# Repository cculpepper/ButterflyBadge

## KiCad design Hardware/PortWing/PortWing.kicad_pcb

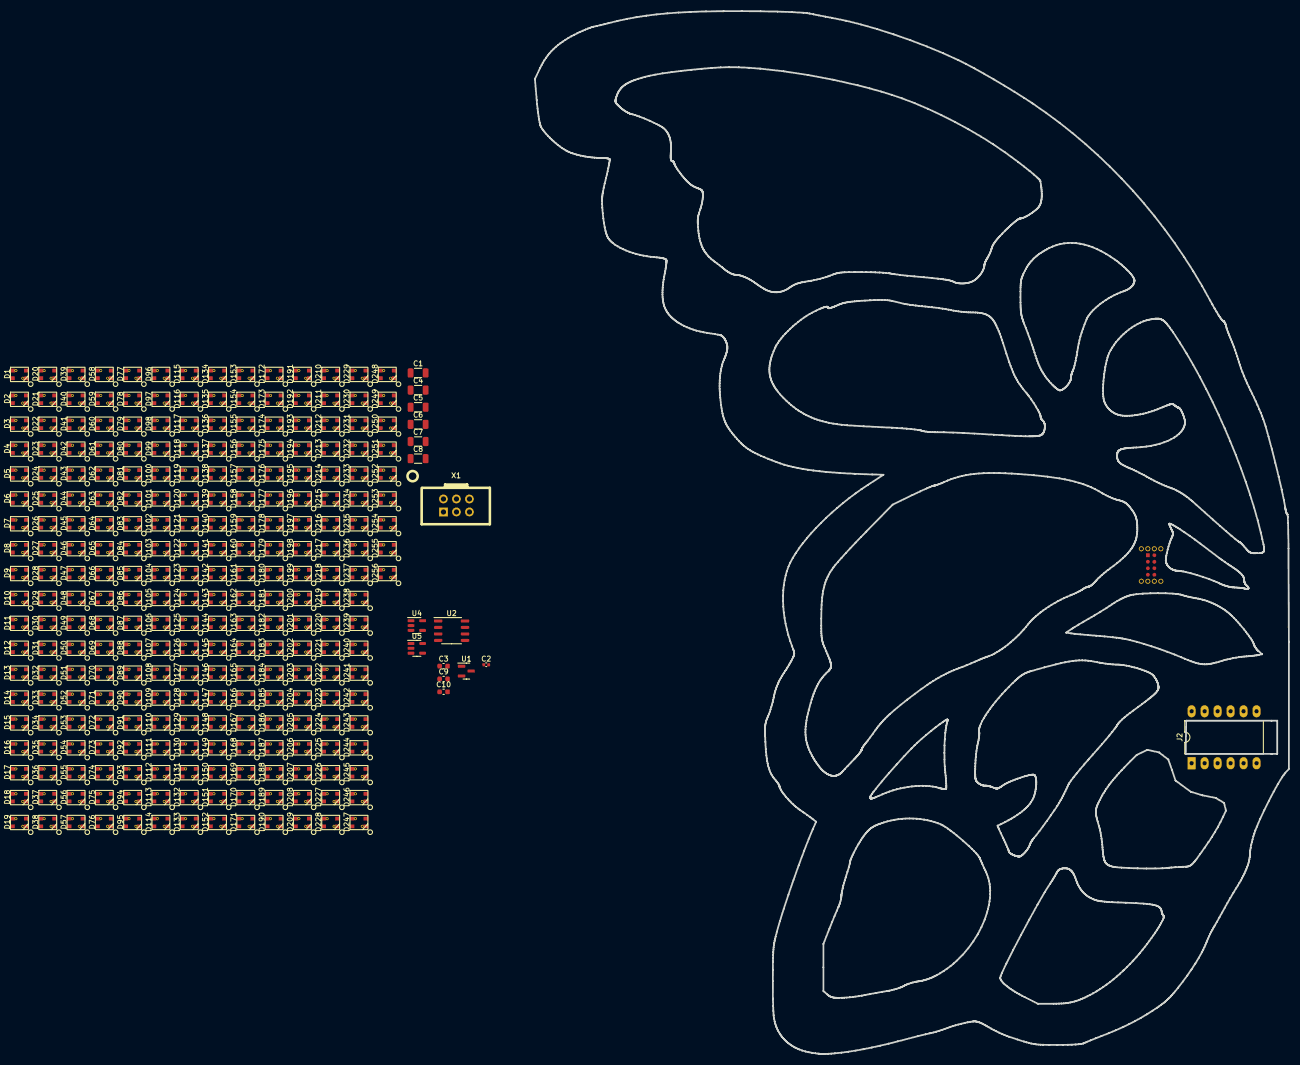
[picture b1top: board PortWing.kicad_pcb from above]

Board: 2 copper layers, 147.4 x 203.9 mm, 273 parts (0 on the bottom side), 265 nets, no tracks yet.

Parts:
C1, C4, C5, C6, C7, C8: 22uF; C_1206_3216Metric
C2: 1uF; C_0402_1005Metric
C3, C9, C10: 10uF; C_0603_1608Metric
D1, D2, D3, D4, D5, D6, D7, D8, D9, D10, D11, D12, D13, D14, D15, D16, D17, D18, D19, D20, D21, D22, D23, D24, D25, D26, D27, D28, D29, D30, D31, D32, D33, D34, D35, D36, D37, D38, D39, D40, D41, D42, D43, D44, D45, D46, D47, D48, D49, D50, D51, D52, D53, D54, D55, D56, D57, D58, D59, D60, D61, D62, D63, D64, D65, D66, D67, D68, D69, D70, D71, D72, D73, D74, D75, D76, D77, D78, D79, D80, D81, D82, D83, D84, D85, D86, D87, D88, D89, D90, D91, D92, D93, D94, D95, D96, D97, D98, D99, D100, D101, D102, D103, D104, D105, D106, D107, D108, D109, D110, D111, D112, D113, D114, D115, D116, D117, D118, D119, D120, D121, D122, D123, D124, D125, D126, D127, D128, D129, D130, D131, D132, D133, D134, D135, D136, D137, D138, D139, D140, D141, D142, D143, D144, D145, D146, D147, D148, D149, D150, D151, D152, D153, D154, D155, D156, D157, D158, D159, D160, D161, D162, D163, D164, D165, D166, D167, D168, D169, D170, D171, D172, D173, D174, D175, D176, D177, D178, D179, D180, D181, D182, D183, D184, D185, D186, D187, D188, D189, D190, D191, D192, D193, D194, D195, D196, D197, D198, D199, D200, D201, D202, D203, D204, D205, D206, D207, D208, D209, D210, D211, D212, D213, D214, D215, D216, D217, D218, D219, D220, D221, D222, D223, D224, D225, D226, D227, D228, D229, D230, D231, D232, D233, D234, D235, D236, D237, D238, D239, D240, D241, D242, D243, D244, D245, D246, D247, D248, D249, D250, D251, D252, D253, D254, D255, D256: SK6812; XL-3528RGBW
J1: Conn_02x04_Odd_Even; FlatFlexWingConnector-WingPCBSide
J2: Conn_02x06_Counter_Clockwise; DIP-12_W10.16mm_LongPads
U1: XC6206PxxxMR; SOT-23
U2: SOP-8_3.9x4.9mm_P1.27mm
U4, U5: SN74LV1T34DBV; SOT-23-5
X1: Badgelife_sao_connector_v169bis; Badgelife-SAOv169-BADGE-2x3

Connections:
/3V3: C2.1, C3.1, C9.1, C10.1, U1.2 (VO), U2.1 (V_EH), U2.8 (VCC), X1.1 (VCC)
/5V: C1.1, C4.1, C5.1, C6.1, C7.1, C8.1, D1.3 (VDD), D2.3 (VDD), D3.3 (VDD), D4.3 (VDD), D5.3 (VDD), D6.3 (VDD), D7.3 (VDD), D8.3 (VDD), D9.3 (VDD), D10.3 (VDD), D11.3 (VDD), D12.3 (VDD), D13.3 (VDD), D14.3 (VDD), D15.3 (VDD), D16.3 (VDD), D17.3 (VDD), D18.3 (VDD), D19.3 (VDD), D20.3 (VDD), D21.3 (VDD), D22.3 (VDD), D23.3 (VDD), D24.3 (VDD), D25.3 (VDD), D26.3 (VDD), D27.3 (VDD), D28.3 (VDD), D29.3 (VDD), D30.3 (VDD), D31.3 (VDD), D32.3 (VDD), D33.3 (VDD), D34.3 (VDD), D35.3 (VDD), D36.3 (VDD), D37.3 (VDD), D38.3 (VDD), D39.3 (VDD), D40.3 (VDD), D41.3 (VDD), D42.3 (VDD), D43.3 (VDD), D44.3 (VDD), D45.3 (VDD), D46.3 (VDD), D47.3 (VDD), D48.3 (VDD), D49.3 (VDD), D50.3 (VDD), D51.3 (VDD), D52.3 (VDD), D53.3 (VDD), D54.3 (VDD), D55.3 (VDD), D56.3 (VDD), D57.3 (VDD), D58.3 (VDD), D59.3 (VDD), D60.3 (VDD), D61.3 (VDD), D62.3 (VDD), D63.3 (VDD), D64.3 (VDD), D65.3 (VDD), D66.3 (VDD), D67.3 (VDD), D68.3 (VDD), D69.3 (VDD), D70.3 (VDD), D71.3 (VDD), D72.3 (VDD), D73.3 (VDD), D74.3 (VDD), D75.3 (VDD), D76.3 (VDD), D77.3 (VDD), D78.3 (VDD), D79.3 (VDD), D80.3 (VDD), D81.3 (VDD), D82.3 (VDD), D83.3 (VDD), D84.3 (VDD), D85.3 (VDD), D86.3 (VDD), D87.3 (VDD), D88.3 (VDD), D89.3 (VDD), D90.3 (VDD), D91.3 (VDD), D92.3 (VDD), D93.3 (VDD), D94.3 (VDD), D95.3 (VDD), D96.3 (VDD), D97.3 (VDD), D98.3 (VDD), D99.3 (VDD), D100.3 (VDD), D101.3 (VDD), D102.3 (VDD), D103.3 (VDD), D104.3 (VDD), D105.3 (VDD), D106.3 (VDD), D107.3 (VDD), D108.3 (VDD), D109.3 (VDD), D110.3 (VDD), D111.3 (VDD), D112.3 (VDD), D113.3 (VDD), D114.3 (VDD), D115.3 (VDD), D116.3 (VDD), D117.3 (VDD), D118.3 (VDD), D119.3 (VDD), D120.3 (VDD), D121.3 (VDD), D122.3 (VDD), D123.3 (VDD), D124.3 (VDD), D125.3 (VDD), D126.3 (VDD), D127.3 (VDD), D128.3 (VDD), D129.3 (VDD), D130.3 (VDD), D131.3 (VDD), D132.3 (VDD), D133.3 (VDD), D134.3 (VDD), D135.3 (VDD), D136.3 (VDD), D137.3 (VDD), D138.3 (VDD), D139.3 (VDD), D140.3 (VDD), D141.3 (VDD), D142.3 (VDD), D143.3 (VDD), D144.3 (VDD), D145.3 (VDD), D146.3 (VDD), D147.3 (VDD), D148.3 (VDD), D149.3 (VDD), D150.3 (VDD), D151.3 (VDD), D152.3 (VDD), D153.3 (VDD), D154.3 (VDD), D155.3 (VDD), D156.3 (VDD), D157.3 (VDD), D158.3 (VDD), D159.3 (VDD), D160.3 (VDD), D161.3 (VDD), D162.3 (VDD), D163.3 (VDD), D164.3 (VDD), D165.3 (VDD), D166.3 (VDD), D167.3 (VDD), D168.3 (VDD), D169.3 (VDD), D170.3 (VDD), D171.3 (VDD), D172.3 (VDD), D173.3 (VDD), D174.3 (VDD), D175.3 (VDD), D176.3 (VDD), D177.3 (VDD), D178.3 (VDD), D179.3 (VDD), D180.3 (VDD), D181.3 (VDD), D182.3 (VDD), D183.3 (VDD), D184.3 (VDD), D185.3 (VDD), D186.3 (VDD), D187.3 (VDD), D188.3 (VDD), D189.3 (VDD), D190.3 (VDD), D191.3 (VDD), D192.3 (VDD), D193.3 (VDD), D194.3 (VDD), D195.3 (VDD), D196.3 (VDD), D197.3 (VDD), D198.3 (VDD), D199.3 (VDD), D200.3 (VDD), D201.3 (VDD), D202.3 (VDD), D203.3 (VDD), D204.3 (VDD), D205.3 (VDD), D206.3 (VDD), D207.3 (VDD), D208.3 (VDD), D209.3 (VDD), D210.3 (VDD), D211.3 (VDD), D212.3 (VDD), D213.3 (VDD), D214.3 (VDD), D215.3 (VDD), D216.3 (VDD), D217.3 (VDD), D218.3 (VDD), D219.3 (VDD), D220.3 (VDD), D221.3 (VDD), D222.3 (VDD), D223.3 (VDD), D224.3 (VDD), D225.3 (VDD), D226.3 (VDD), D227.3 (VDD), D228.3 (VDD), D229.3 (VDD), D230.3 (VDD), D231.3 (VDD), D232.3 (VDD), D233.3 (VDD), D234.3 (VDD), D235.3 (VDD), D236.3 (VDD), D237.3 (VDD), D238.3 (VDD), D239.3 (VDD), D240.3 (VDD), D241.3 (VDD), D242.3 (VDD), D243.3 (VDD), D244.3 (VDD), D245.3 (VDD), D246.3 (VDD), D247.3 (VDD), D248.3 (VDD), D249.3 (VDD), D250.3 (VDD), D251.3 (VDD), D252.3 (VDD), D253.3 (VDD), D254.3 (VDD), D255.3 (VDD), D256.3 (VDD), J1.1, U1.3 (VI), U4.5 (VCC), U5.5 (VCC)
/GND: C1.2, C2.2, C3.2, C4.2, C5.2, C6.2, C7.2, C8.2, C9.2, C10.2, D1.1 (VSS), D2.1 (VSS), D3.1 (VSS), D4.1 (VSS), D5.1 (VSS), D6.1 (VSS), D7.1 (VSS), D8.1 (VSS), D9.1 (VSS), D10.1 (VSS), D11.1 (VSS), D12.1 (VSS), D13.1 (VSS), D14.1 (VSS), D15.1 (VSS), D16.1 (VSS), D17.1 (VSS), D18.1 (VSS), D19.1 (VSS), D20.1 (VSS), D21.1 (VSS), D22.1 (VSS), D23.1 (VSS), D24.1 (VSS), D25.1 (VSS), D26.1 (VSS), D27.1 (VSS), D28.1 (VSS), D29.1 (VSS), D30.1 (VSS), D31.1 (VSS), D32.1 (VSS), D33.1 (VSS), D34.1 (VSS), D35.1 (VSS), D36.1 (VSS), D37.1 (VSS), D38.1 (VSS), D39.1 (VSS), D40.1 (VSS), D41.1 (VSS), D42.1 (VSS), D43.1 (VSS), D44.1 (VSS), D45.1 (VSS), D46.1 (VSS), D47.1 (VSS), D48.1 (VSS), D49.1 (VSS), D50.1 (VSS), D51.1 (VSS), D52.1 (VSS), D53.1 (VSS), D54.1 (VSS), D55.1 (VSS), D56.1 (VSS), D57.1 (VSS), D58.1 (VSS), D59.1 (VSS), D60.1 (VSS), D61.1 (VSS), D62.1 (VSS), D63.1 (VSS), D64.1 (VSS), D65.1 (VSS), D66.1 (VSS), D67.1 (VSS), D68.1 (VSS), D69.1 (VSS), D70.1 (VSS), D71.1 (VSS), D72.1 (VSS), D73.1 (VSS), D74.1 (VSS), D75.1 (VSS), D76.1 (VSS), D77.1 (VSS), D78.1 (VSS), D79.1 (VSS), D80.1 (VSS), D81.1 (VSS), D82.1 (VSS), D83.1 (VSS), D84.1 (VSS), D85.1 (VSS), D86.1 (VSS), D87.1 (VSS), D88.1 (VSS), D89.1 (VSS), D90.1 (VSS), D91.1 (VSS), D92.1 (VSS), D93.1 (VSS), D94.1 (VSS), D95.1 (VSS), D96.1 (VSS), D97.1 (VSS), D98.1 (VSS), D99.1 (VSS), D100.1 (VSS), D101.1 (VSS), D102.1 (VSS), D103.1 (VSS), D104.1 (VSS), D105.1 (VSS), D106.1 (VSS), D107.1 (VSS), D108.1 (VSS), D109.1 (VSS), D110.1 (VSS), D111.1 (VSS), D112.1 (VSS), D113.1 (VSS), D114.1 (VSS), D115.1 (VSS), D116.1 (VSS), D117.1 (VSS), D118.1 (VSS), D119.1 (VSS), D120.1 (VSS), D121.1 (VSS), D122.1 (VSS), D123.1 (VSS), D124.1 (VSS), D125.1 (VSS), D126.1 (VSS), D127.1 (VSS), D128.1 (VSS), D129.1 (VSS), D130.1 (VSS), D131.1 (VSS), D132.1 (VSS), D133.1 (VSS), D134.1 (VSS), D135.1 (VSS), D136.1 (VSS), D137.1 (VSS), D138.1 (VSS), D139.1 (VSS), D140.1 (VSS), D141.1 (VSS), D142.1 (VSS), D143.1 (VSS), D144.1 (VSS), D145.1 (VSS), D146.1 (VSS), D147.1 (VSS), D148.1 (VSS), D149.1 (VSS), D150.1 (VSS), D151.1 (VSS), D152.1 (VSS), D153.1 (VSS), D154.1 (VSS), D155.1 (VSS), D156.1 (VSS), D157.1 (VSS), D158.1 (VSS), D159.1 (VSS), D160.1 (VSS), D161.1 (VSS), D162.1 (VSS), D163.1 (VSS), D164.1 (VSS), D165.1 (VSS), D166.1 (VSS), D167.1 (VSS), D168.1 (VSS), D169.1 (VSS), D170.1 (VSS), D171.1 (VSS), D172.1 (VSS), D173.1 (VSS), D174.1 (VSS), D175.1 (VSS), D176.1 (VSS), D177.1 (VSS), D178.1 (VSS), D179.1 (VSS), D180.1 (VSS), D181.1 (VSS), D182.1 (VSS), D183.1 (VSS), D184.1 (VSS), D185.1 (VSS), D186.1 (VSS), D187.1 (VSS), D188.1 (VSS), D189.1 (VSS), D190.1 (VSS), D191.1 (VSS), D192.1 (VSS), D193.1 (VSS), D194.1 (VSS), D195.1 (VSS), D196.1 (VSS), D197.1 (VSS), D198.1 (VSS), D199.1 (VSS), D200.1 (VSS), D201.1 (VSS), D202.1 (VSS), D203.1 (VSS), D204.1 (VSS), D205.1 (VSS), D206.1 (VSS), D207.1 (VSS), D208.1 (VSS), D209.1 (VSS), D210.1 (VSS), D211.1 (VSS), D212.1 (VSS), D213.1 (VSS), D214.1 (VSS), D215.1 (VSS), D216.1 (VSS), D217.1 (VSS), D218.1 (VSS), D219.1 (VSS), D220.1 (VSS), D221.1 (VSS), D222.1 (VSS), D223.1 (VSS), D224.1 (VSS), D225.1 (VSS), D226.1 (VSS), D227.1 (VSS), D228.1 (VSS), D229.1 (VSS), D230.1 (VSS), D231.1 (VSS), D232.1 (VSS), D233.1 (VSS), D234.1 (VSS), D235.1 (VSS), D236.1 (VSS), D237.1 (VSS), D238.1 (VSS), D239.1 (VSS), D240.1 (VSS), D241.1 (VSS), D242.1 (VSS), D243.1 (VSS), D244.1 (VSS), D245.1 (VSS), D246.1 (VSS), D247.1 (VSS), D248.1 (VSS), D249.1 (VSS), D250.1 (VSS), D251.1 (VSS), D252.1 (VSS), D253.1 (VSS), D254.1 (VSS), D255.1 (VSS), D256.1 (VSS), J1.3, U1.1 (GND), U2.4 (VSS), U4.3 (GND), U5.3 (GND), X1.2 (GND)
/NFC_MSG: J1.8, U2.7 (GP0), X1.6 (GPIO2)
/PORT_GP0: J1.6, X1.5 (GPIO1)
/PORT_LED_1: J1.2, U4.2 (A)
/PORT_LED_2: J1.4, U5.2 (A)
/SCL: J1.5, U2.6 (SCL), X1.4 (SCL)
/SDA: J1.7, U2.5 (SDA), X1.3 (SDA)
unnamed: D1.2 (DIN), U4.4 (Y)
unnamed: D1.4 (DOUT), D2.2 (DIN)
unnamed: D2.4 (DOUT), D3.2 (DIN)
unnamed: D3.4 (DOUT), D4.2 (DIN)
unnamed: D4.4 (DOUT), D5.2 (DIN)
unnamed: D5.4 (DOUT), D6.2 (DIN)
unnamed: D6.4 (DOUT), D7.2 (DIN)
unnamed: D7.4 (DOUT), D8.2 (DIN)
unnamed: D8.4 (DOUT), D9.2 (DIN)
unnamed: D9.4 (DOUT), D10.2 (DIN)
unnamed: D10.4 (DOUT), D11.2 (DIN)
unnamed: D11.4 (DOUT), D12.2 (DIN)
unnamed: D12.4 (DOUT), D13.2 (DIN)
unnamed: D13.4 (DOUT), D14.2 (DIN)
unnamed: D14.4 (DOUT), D15.2 (DIN)
unnamed: D15.4 (DOUT), D16.2 (DIN)
unnamed: D16.4 (DOUT), D17.2 (DIN)
unnamed: D17.4 (DOUT), D18.2 (DIN)
unnamed: D18.4 (DOUT), D19.2 (DIN)
unnamed: D19.4 (DOUT), D20.2 (DIN)
unnamed: D20.4 (DOUT), D21.2 (DIN)
unnamed: D21.4 (DOUT), D22.2 (DIN)
unnamed: D22.4 (DOUT), D23.2 (DIN)
unnamed: D23.4 (DOUT), D24.2 (DIN)
unnamed: D24.4 (DOUT), D25.2 (DIN)
unnamed: D25.4 (DOUT), D26.2 (DIN)
unnamed: D26.4 (DOUT), D27.2 (DIN)
unnamed: D27.4 (DOUT), D28.2 (DIN)
unnamed: D28.4 (DOUT), D29.2 (DIN)
unnamed: D29.4 (DOUT), D30.2 (DIN)
unnamed: D30.4 (DOUT), D31.2 (DIN)
unnamed: D31.4 (DOUT), D32.2 (DIN)
unnamed: D32.4 (DOUT), D33.2 (DIN)
unnamed: D33.4 (DOUT), D34.2 (DIN)
unnamed: D34.4 (DOUT), D35.2 (DIN)
unnamed: D35.4 (DOUT), D36.2 (DIN)
unnamed: D36.4 (DOUT), D37.2 (DIN)
unnamed: D37.4 (DOUT), D38.2 (DIN)
unnamed: D38.4 (DOUT), D39.2 (DIN)
unnamed: D39.4 (DOUT), D40.2 (DIN)
unnamed: D40.4 (DOUT), D41.2 (DIN)
unnamed: D41.4 (DOUT), D42.2 (DIN)
unnamed: D42.4 (DOUT), D43.2 (DIN)
unnamed: D43.4 (DOUT), D44.2 (DIN)
unnamed: D44.4 (DOUT), D45.2 (DIN)
unnamed: D45.4 (DOUT), D46.2 (DIN)
unnamed: D46.4 (DOUT), D47.2 (DIN)
unnamed: D47.4 (DOUT), D48.2 (DIN)
unnamed: D48.4 (DOUT), D49.2 (DIN)
unnamed: D49.4 (DOUT), D50.2 (DIN)
unnamed: D50.4 (DOUT), D51.2 (DIN)
unnamed: D51.4 (DOUT), D52.2 (DIN)
unnamed: D52.4 (DOUT), D53.2 (DIN)
unnamed: D53.4 (DOUT), D54.2 (DIN)
unnamed: D54.4 (DOUT), D55.2 (DIN)
unnamed: D55.4 (DOUT), D56.2 (DIN)
unnamed: D56.4 (DOUT), D57.2 (DIN)
unnamed: D57.4 (DOUT), D58.2 (DIN)
unnamed: D58.4 (DOUT), D59.2 (DIN)
unnamed: D59.4 (DOUT), D60.2 (DIN)
unnamed: D60.4 (DOUT), D61.2 (DIN)
unnamed: D61.4 (DOUT), D62.2 (DIN)
unnamed: D62.4 (DOUT), D63.2 (DIN)
unnamed: D63.4 (DOUT), D64.2 (DIN)
unnamed: D64.4 (DOUT), D65.2 (DIN)
unnamed: D65.4 (DOUT), D66.2 (DIN)
unnamed: D66.4 (DOUT), D67.2 (DIN)
unnamed: D67.4 (DOUT), D68.2 (DIN)
unnamed: D68.4 (DOUT), D69.2 (DIN)
unnamed: D69.4 (DOUT), D70.2 (DIN)
unnamed: D70.4 (DOUT), D71.2 (DIN)
unnamed: D71.4 (DOUT), D72.2 (DIN)
unnamed: D72.4 (DOUT), D73.2 (DIN)
unnamed: D73.4 (DOUT), D74.2 (DIN)
unnamed: D74.4 (DOUT), D75.2 (DIN)
unnamed: D75.4 (DOUT), D76.2 (DIN)
unnamed: D76.4 (DOUT), D77.2 (DIN)
unnamed: D77.4 (DOUT), D78.2 (DIN)
unnamed: D78.4 (DOUT), D79.2 (DIN)
unnamed: D79.4 (DOUT), D80.2 (DIN)
unnamed: D80.4 (DOUT), D81.2 (DIN)
unnamed: D81.4 (DOUT), D82.2 (DIN)
unnamed: D82.4 (DOUT), D83.2 (DIN)
unnamed: D83.4 (DOUT), D84.2 (DIN)
unnamed: D84.4 (DOUT), D85.2 (DIN)
unnamed: D85.4 (DOUT), D86.2 (DIN)
unnamed: D86.4 (DOUT), D87.2 (DIN)
unnamed: D87.4 (DOUT), D88.2 (DIN)
unnamed: D88.4 (DOUT), D89.2 (DIN)
unnamed: D89.4 (DOUT), D90.2 (DIN)
unnamed: D90.4 (DOUT), D91.2 (DIN)
unnamed: D91.4 (DOUT), D92.2 (DIN)
unnamed: D92.4 (DOUT), D93.2 (DIN)
unnamed: D93.4 (DOUT), D94.2 (DIN)
unnamed: D94.4 (DOUT), D95.2 (DIN)
unnamed: D95.4 (DOUT), D96.2 (DIN)
unnamed: D96.4 (DOUT), D97.2 (DIN)
unnamed: D97.4 (DOUT), D98.2 (DIN)
unnamed: D98.4 (DOUT), D99.2 (DIN)
unnamed: D99.4 (DOUT), D100.2 (DIN)
unnamed: D100.4 (DOUT), D101.2 (DIN)
unnamed: D101.4 (DOUT), D102.2 (DIN)
unnamed: D102.4 (DOUT), D103.2 (DIN)
unnamed: D103.4 (DOUT), D104.2 (DIN)
unnamed: D104.4 (DOUT), D105.2 (DIN)
unnamed: D105.4 (DOUT), D106.2 (DIN)
unnamed: D106.4 (DOUT), D107.2 (DIN)
unnamed: D107.4 (DOUT), D108.2 (DIN)
unnamed: D108.4 (DOUT), D109.2 (DIN)
unnamed: D109.4 (DOUT), D110.2 (DIN)
unnamed: D110.4 (DOUT), D111.2 (DIN)
unnamed: D111.4 (DOUT), D112.2 (DIN)
unnamed: D112.4 (DOUT), D113.2 (DIN)
unnamed: D113.4 (DOUT), D114.2 (DIN)
unnamed: D114.4 (DOUT), D115.2 (DIN)
unnamed: D115.4 (DOUT), D116.2 (DIN)
unnamed: D116.4 (DOUT), D117.2 (DIN)
unnamed: D117.4 (DOUT), D118.2 (DIN)
unnamed: D118.4 (DOUT), D119.2 (DIN)
unnamed: D119.4 (DOUT), D120.2 (DIN)
unnamed: D120.4 (DOUT), D121.2 (DIN)
unnamed: D121.4 (DOUT), D122.2 (DIN)
unnamed: D122.4 (DOUT), D123.2 (DIN)
unnamed: D123.4 (DOUT), D124.2 (DIN)
unnamed: D124.4 (DOUT), D125.2 (DIN)
unnamed: D125.4 (DOUT), D126.2 (DIN)
unnamed: D126.4 (DOUT), D127.2 (DIN)
unnamed: D127.4 (DOUT), D128.2 (DIN)
unnamed: D129.2 (DIN), U5.4 (Y)
unnamed: D129.4 (DOUT), D130.2 (DIN)
unnamed: D130.4 (DOUT), D131.2 (DIN)
unnamed: D131.4 (DOUT), D132.2 (DIN)
unnamed: D132.4 (DOUT), D133.2 (DIN)
unnamed: D133.4 (DOUT), D134.2 (DIN)
unnamed: D134.4 (DOUT), D135.2 (DIN)
unnamed: D135.4 (DOUT), D136.2 (DIN)
unnamed: D136.4 (DOUT), D137.2 (DIN)
unnamed: D137.4 (DOUT), D138.2 (DIN)
unnamed: D138.4 (DOUT), D139.2 (DIN)
unnamed: D139.4 (DOUT), D140.2 (DIN)
unnamed: D140.4 (DOUT), D141.2 (DIN)
unnamed: D141.4 (DOUT), D142.2 (DIN)
unnamed: D142.4 (DOUT), D143.2 (DIN)
unnamed: D143.4 (DOUT), D144.2 (DIN)
unnamed: D144.4 (DOUT), D145.2 (DIN)
unnamed: D145.4 (DOUT), D146.2 (DIN)
unnamed: D146.4 (DOUT), D147.2 (DIN)
unnamed: D147.4 (DOUT), D148.2 (DIN)
unnamed: D148.4 (DOUT), D149.2 (DIN)
unnamed: D149.4 (DOUT), D150.2 (DIN)
unnamed: D150.4 (DOUT), D151.2 (DIN)
unnamed: D151.4 (DOUT), D152.2 (DIN)
unnamed: D152.4 (DOUT), D153.2 (DIN)
unnamed: D153.4 (DOUT), D154.2 (DIN)
unnamed: D154.4 (DOUT), D155.2 (DIN)
unnamed: D155.4 (DOUT), D156.2 (DIN)
unnamed: D156.4 (DOUT), D157.2 (DIN)
unnamed: D157.4 (DOUT), D158.2 (DIN)
unnamed: D158.4 (DOUT), D159.2 (DIN)
unnamed: D159.4 (DOUT), D160.2 (DIN)
unnamed: D160.4 (DOUT), D161.2 (DIN)
unnamed: D161.4 (DOUT), D162.2 (DIN)
unnamed: D162.4 (DOUT), D163.2 (DIN)
unnamed: D163.4 (DOUT), D164.2 (DIN)
unnamed: D164.4 (DOUT), D165.2 (DIN)
unnamed: D165.4 (DOUT), D166.2 (DIN)
unnamed: D166.4 (DOUT), D167.2 (DIN)
unnamed: D167.4 (DOUT), D168.2 (DIN)
unnamed: D168.4 (DOUT), D169.2 (DIN)
unnamed: D169.4 (DOUT), D170.2 (DIN)
unnamed: D170.4 (DOUT), D171.2 (DIN)
unnamed: D171.4 (DOUT), D172.2 (DIN)
unnamed: D172.4 (DOUT), D173.2 (DIN)
unnamed: D173.4 (DOUT), D174.2 (DIN)
unnamed: D174.4 (DOUT), D175.2 (DIN)
unnamed: D175.4 (DOUT), D176.2 (DIN)
unnamed: D176.4 (DOUT), D177.2 (DIN)
unnamed: D177.4 (DOUT), D178.2 (DIN)
unnamed: D178.4 (DOUT), D179.2 (DIN)
unnamed: D179.4 (DOUT), D180.2 (DIN)
unnamed: D180.4 (DOUT), D181.2 (DIN)
unnamed: D181.4 (DOUT), D182.2 (DIN)
unnamed: D182.4 (DOUT), D183.2 (DIN)
unnamed: D183.4 (DOUT), D184.2 (DIN)
unnamed: D184.4 (DOUT), D185.2 (DIN)
unnamed: D185.4 (DOUT), D186.2 (DIN)
unnamed: D186.4 (DOUT), D187.2 (DIN)
unnamed: D187.4 (DOUT), D188.2 (DIN)
unnamed: D188.4 (DOUT), D189.2 (DIN)
unnamed: D189.4 (DOUT), D190.2 (DIN)
unnamed: D190.4 (DOUT), D191.2 (DIN)
unnamed: D191.4 (DOUT), D192.2 (DIN)
unnamed: D192.4 (DOUT), D193.2 (DIN)
unnamed: D193.4 (DOUT), D194.2 (DIN)
unnamed: D194.4 (DOUT), D195.2 (DIN)
unnamed: D195.4 (DOUT), D196.2 (DIN)
unnamed: D196.4 (DOUT), D197.2 (DIN)
unnamed: D197.4 (DOUT), D198.2 (DIN)
unnamed: D198.4 (DOUT), D199.2 (DIN)
unnamed: D199.4 (DOUT), D200.2 (DIN)
unnamed: D200.4 (DOUT), D201.2 (DIN)
unnamed: D201.4 (DOUT), D202.2 (DIN)
unnamed: D202.4 (DOUT), D203.2 (DIN)
unnamed: D203.4 (DOUT), D204.2 (DIN)
unnamed: D204.4 (DOUT), D205.2 (DIN)
unnamed: D205.4 (DOUT), D206.2 (DIN)
unnamed: D206.4 (DOUT), D207.2 (DIN)
unnamed: D207.4 (DOUT), D208.2 (DIN)
unnamed: D208.4 (DOUT), D209.2 (DIN)
unnamed: D209.4 (DOUT), D210.2 (DIN)
unnamed: D210.4 (DOUT), D211.2 (DIN)
unnamed: D211.4 (DOUT), D212.2 (DIN)
unnamed: D212.4 (DOUT), D213.2 (DIN)
unnamed: D213.4 (DOUT), D214.2 (DIN)
unnamed: D214.4 (DOUT), D215.2 (DIN)
unnamed: D215.4 (DOUT), D216.2 (DIN)
unnamed: D216.4 (DOUT), D217.2 (DIN)
unnamed: D217.4 (DOUT), D218.2 (DIN)
unnamed: D218.4 (DOUT), D219.2 (DIN)
unnamed: D219.4 (DOUT), D220.2 (DIN)
unnamed: D220.4 (DOUT), D221.2 (DIN)
unnamed: D221.4 (DOUT), D222.2 (DIN)
unnamed: D222.4 (DOUT), D223.2 (DIN)
unnamed: D223.4 (DOUT), D224.2 (DIN)
unnamed: D224.4 (DOUT), D225.2 (DIN)
unnamed: D225.4 (DOUT), D226.2 (DIN)
unnamed: D226.4 (DOUT), D227.2 (DIN)
unnamed: D227.4 (DOUT), D228.2 (DIN)
unnamed: D228.4 (DOUT), D229.2 (DIN)
unnamed: D229.4 (DOUT), D230.2 (DIN)
unnamed: D230.4 (DOUT), D231.2 (DIN)
unnamed: D231.4 (DOUT), D232.2 (DIN)
unnamed: D232.4 (DOUT), D233.2 (DIN)
unnamed: D233.4 (DOUT), D234.2 (DIN)
unnamed: D234.4 (DOUT), D235.2 (DIN)
unnamed: D235.4 (DOUT), D236.2 (DIN)
unnamed: D236.4 (DOUT), D237.2 (DIN)
unnamed: D237.4 (DOUT), D238.2 (DIN)
unnamed: D238.4 (DOUT), D239.2 (DIN)
unnamed: D239.4 (DOUT), D240.2 (DIN)
unnamed: D240.4 (DOUT), D241.2 (DIN)
unnamed: D241.4 (DOUT), D242.2 (DIN)
unnamed: D242.4 (DOUT), D243.2 (DIN)
unnamed: D243.4 (DOUT), D244.2 (DIN)
unnamed: D244.4 (DOUT), D245.2 (DIN)
unnamed: D245.4 (DOUT), D246.2 (DIN)
unnamed: D246.4 (DOUT), D247.2 (DIN)
unnamed: D247.4 (DOUT), D248.2 (DIN)
unnamed: D248.4 (DOUT), D249.2 (DIN)
unnamed: D249.4 (DOUT), D250.2 (DIN)
unnamed: D250.4 (DOUT), D251.2 (DIN)
unnamed: D251.4 (DOUT), D252.2 (DIN)
unnamed: D252.4 (DOUT), D253.2 (DIN)
unnamed: D253.4 (DOUT), D254.2 (DIN)
unnamed: D254.4 (DOUT), D255.2 (DIN)
unnamed: D255.4 (DOUT), D256.2 (DIN)

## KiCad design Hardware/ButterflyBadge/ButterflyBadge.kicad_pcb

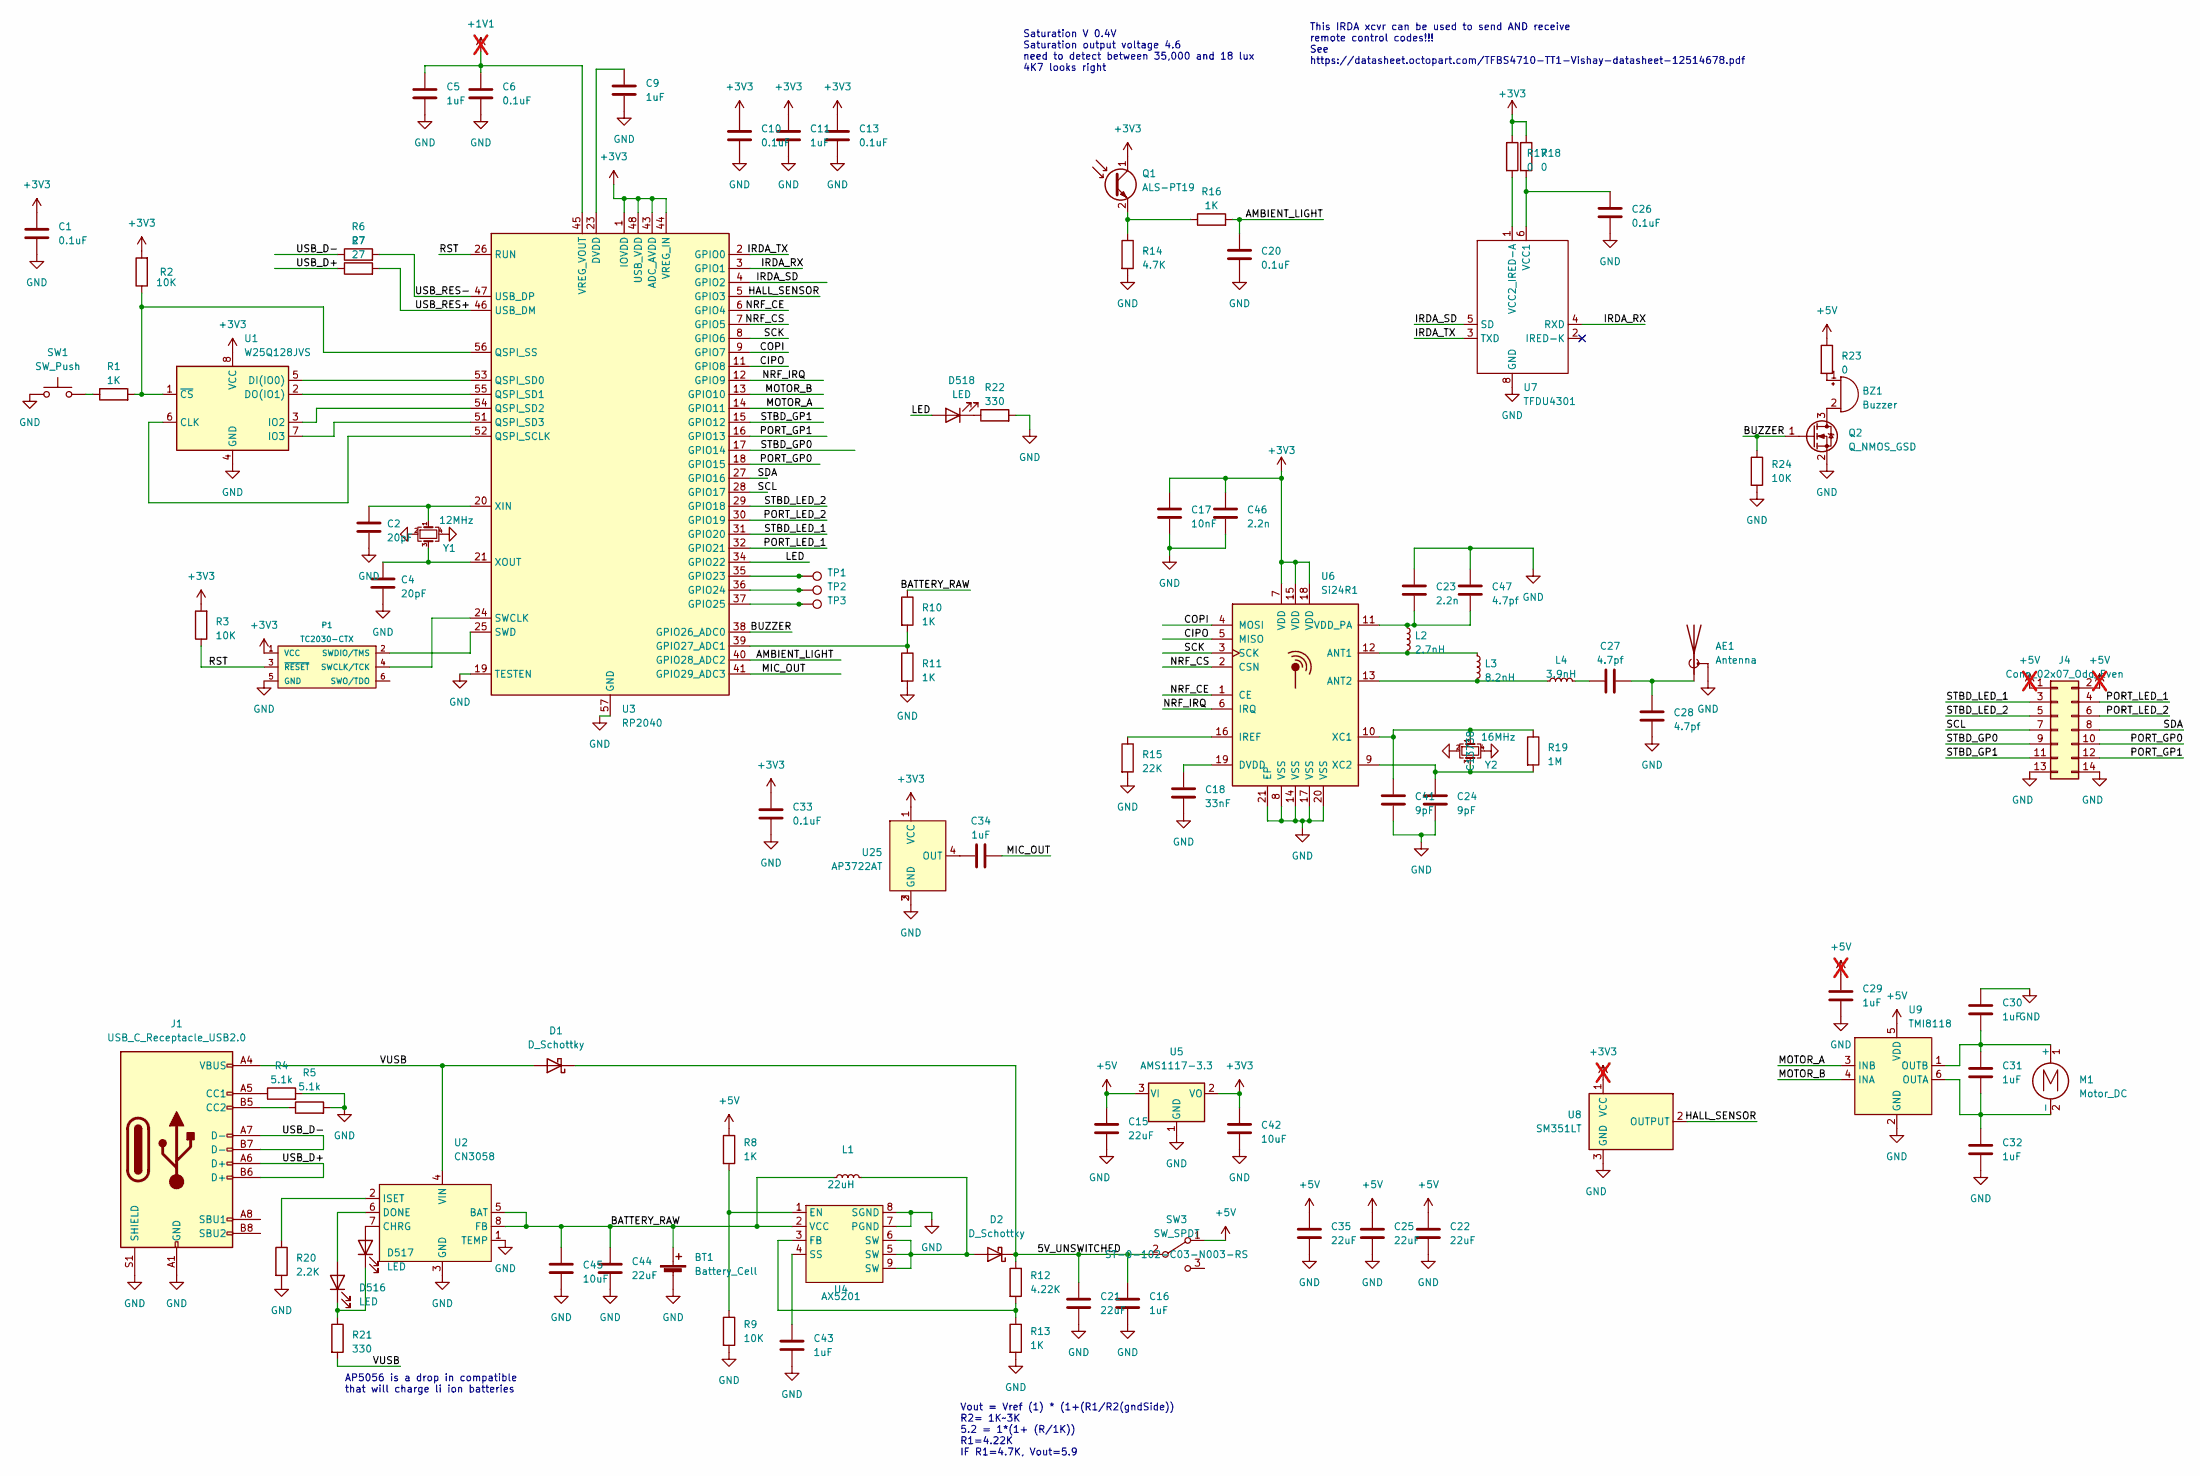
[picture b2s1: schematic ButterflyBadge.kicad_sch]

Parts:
AE1: Antenna; Texas_SWRA117D_2.4GHz_Left
BT1: Battery_Cell; BatteryHolder_MPD_BH-18650-PC2
BZ1: Buzzer; Buzzer-GSC5025YA-12R4000
C1, C6, C10, C13, C20, C33: 0.1uF; C_0402_1005Metric; LCSC C307331
C2, C4: 20pF; C_0402_1005Metric; LCSC C1554
C5, C9, C11, C16, C29, C30, C31, C32, C34, C43: 1uF; C_0402_1005Metric; LCSC C52923
C15, C21, C22, C25, C35, C44: 22uF; C_1206_3216Metric; LCSC C12891
C17: 10nF; C_0402_1005Metric; LCSC C15195
C18: 33nF; C_0402_1005Metric; LCSC C1585
C23, C46: 2.2n; C_0402_1005Metric; LCSC C1531
C24, C41: 9pF; C_0402_1005Metric; LCSC C32949
C26: 0.1uF; C_0603_1608Metric; LCSC C307331
C27, C28, C47: 4.7pf; C_0402_1005Metric; LCSC C1569
C42, C45: 10uF; C_0603_1608Metric; LCSC C96446
D1, D2: D_Schottky; D_SMA; LCSC C8678
D516, D517, D518: LED; LED_0603_1608Metric; LCSC C2286
J1: USB_C_Receptacle_USB2.0; USB_C_Receptacle_HRO_TYPE-C-31-M-12
J4: Conn_02x07_Odd_Even; FlatFlexWingConnector-PCBSide
L1: 22uH; YSPI0630A; LCSC C497873
L2: 2.7nH; L_0402_1005Metric; LCSC C14033
L3: 8.2nH; L_0402_1005Metric; LCSC C27147
L4: 3.9nH; L_0402_1005Metric; LCSC C14033
M1: Motor_DC; JST_XH_B2B-XH-AM_1x02_P2.50mm_Vertical
P1: TC2030-CTX; TC2030-MCP-NL
Q1: ALS-PT19; R_0402_1005Metric; Manufacturer PN ALS-PT19-315C/L177/TR8; LCSC C146233
Q2: Q_NMOS_GSD; SOT-23; LCSC C8545
R1, R8, R10, R11, R13, R16: 1K; R_0402_1005Metric; LCSC C11702
R2, R3, R9, R24: 10K; R_0402_1005Metric; LCSC C25744
R4, R5: 5.1k; R_0402_1005Metric; LCSC C25905
R6, R7: 27; R_0402_1005Metric; LCSC C25105
R12: 4.22K; R_0402_1005Metric; LCSC C25900
R14: 4.7K; R_0402_1005Metric; LCSC C25900
R15: 22K; R_0402_1005Metric; LCSC C25768
R17, R18, R23: 0; R_0402_1005Metric; LCSC C17168
R19: 1M; R_0402_1005Metric; LCSC C26083
R20: 2.2K; C_0402_1005Metric; LCSC C25879
R21, R22: 330; C_0402_1005Metric; LCSC C25104
SW1: SW_Push; SW_SPST_EVPBF; LCSC C318884
SW3: SW_SPDT; SW_Push_1P2T_Vertical_E-Switch_800UDP8P1A1M6; Manufacturer PN ST-0-102-C03-N003-RS
TP1, TP2, TP3: TestPoint_Pad_D1.0mm
U1: W25Q128JVS; SOIC-8_5.23x5.23mm_P1.27mm; LCSC C97521
U2: CN3058; SOP-8_3.9x4.9mm_P1.27mm; LCSC CN3058E
U3: RP2040; QFN-56-1EP_7x7mm_P0.4mm_EP3.2x3.2mm; LCSC C2040
U4: AX5201; SOIC-8-1EP_3.9x4.9mm_P1.27mm_EP2.41x3.3mm_ThermalVias; LCSC C211668
U5: AMS1117-3.3; SOT-223-3_TabPin2; LCSC C6186
U6: Si24R1; QFN-20-1EP_4x4mm_P0.5mm_EP2.5x2.5mm; LCSC C14436
U7: TFDU4301; LCSC C222418
U8: SM351LT; SOT-23; LCSC C285995
U9: TMI8118; SOT-23-6; LCSC C840556
U25: AP3722AT; LCSC C918198
Y1: 12MHz; Crystal_SMD_3225-4Pin_3.2x2.5mm; LCSC C9002
Y2: 16MHz; Crystal_SMD_3225-4Pin_3.2x2.5mm; LCSC C13738

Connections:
+1V1: C5.1, C6.1, U3.45 (VREG_VOUT)
+3V3: C1.1, C10.1, C11.1, C13.1, C17.1, C33.1, C42.1, C46.1, P1.1 (VCC), Q1.1 (C), R2.2, R3.2, R17.1, R18.1, U1.8 (VCC), U3.1 (IOVDD), U3.10 (IOVDD), U3.22 (IOVDD), U3.33 (IOVDD), U3.42 (IOVDD), U3.43 (ADC_AVDD), U3.44 (VREG_IN), U3.48 (USB_VDD), U3.49 (IOVDD), U5.2 (VO), U6.7 (VDD), U6.15 (VDD), U6.18 (VDD), U8.1 (VCC), U25.1 (VCC)
+5V: C15.1, C22.1, C25.1, C29.1, C35.1, J4.1, J4.2, R8.1, R23.1, SW3.1 (A), U5.3 (VI), U9.5 (VDD)
/5V_UNSWITCHED: C16.1, C21.1, D1.1 (K), D2.1 (K), R12.1, SW3.2 (B)
/AMBIENT_LIGHT: C20.1, R16.2, U3.40 (GPIO28_ADC2)
/BATTERY_RAW: BT1.1 (+), C44.1, C45.1, L1.1, R10.1, U2.5 (BAT), U2.8 (FB), U4.2 (VCC)
/BUZZER: Q2.1 (G), R24.1, U3.38 (GPIO26_ADC0)
/CIPO: U3.11 (GPIO8), U6.5 (MISO)
/COPI: U3.9 (GPIO7), U6.4 (MOSI)
/HALL_SENSOR: U3.5 (GPIO3), U8.2 (OUTPUT)
/IRDA_RX: U3.3 (GPIO1), U7.4 (RXD)
/IRDA_SD: U3.4 (GPIO2), U7.5 (SD)
/IRDA_TX: U3.2 (GPIO0), U7.3 (TXD)
/LED: D518.2 (A), U3.34 (GPIO22)
/MIC_OUT: C34.2, U3.41 (GPIO29_ADC3)
/MOTOR_A: U3.14 (GPIO11), U9.3 (INB)
/MOTOR_B: U3.13 (GPIO10), U9.4 (INA)
/NRF_CE: U3.6 (GPIO4), U6.1 (CE)
/NRF_CS: U3.7 (GPIO5), U6.2 (CSN)
/NRF_IRQ: U3.12 (GPIO9), U6.6 (IRQ)
/PORT_GP0: J4.10, U3.18 (GPIO15)
/PORT_GP1: J4.12, U3.16 (GPIO13)
/PORT_LED_1: J4.4, U3.32 (GPIO21)
/PORT_LED_2: J4.6, U3.30 (GPIO19)
/RST: P1.3 (~RESET), R3.1, U3.26 (RUN)
/SCK: U3.8 (GPIO6), U6.3 (SCK)
/SCL: J4.7, U3.28 (GPIO17)
/SDA: J4.8, U3.27 (GPIO16)
/STBD_GP0: J4.9, U3.17 (GPIO14)
/STBD_GP1: J4.11, U3.15 (GPIO12)
/STBD_LED_1: J4.3, U3.31 (GPIO20)
/STBD_LED_2: J4.5, U3.29 (GPIO18)
/USB_D+: J1.A6 (D+), J1.B6 (D+), R7.1
/USB_D-: J1.A7 (D-), J1.B7 (D-), R6.1
/USB_RES+: R7.2, U3.46 (USB_DM)
/USB_RES-: R6.2, U3.47 (USB_DP)
/VUSB: D1.2 (A), J1.A4 (VBUS), J1.A9 (VBUS), J1.B4 (VBUS), J1.B9 (VBUS), R21.2, U2.4 (VIN)
GND: AE1.2 (Shield), BT1.2 (-), C1.2, C2.2, C4.2, C5.2, C6.2, C9.2, C10.2, C11.2, C13.2, C15.2, C16.2, C17.2, C18.2, C20.2, C21.2, C22.2, C23.1, C24.2, C25.2, C26.2, C28.1, C29.2, C30.1, C32.2, C33.2, C35.2, C41.2, C42.2, C43.2, C44.2, C45.2, C46.2, C47.2, J1.A1 (GND), J1.A12 (GND), J1.B1 (GND), J1.B12 (GND), J1.S1 (SHIELD), J4.13, J4.14, P1.5 (GND), Q2.2 (S), R4.2, R5.2, R9.2, R11.2, R13.2, R14.2, R15.2, R20.2, R22.2, R24.2, SW1.1, U1.4 (GND), U2.1 (TEMP), U2.3 (GND), U3.19 (TESTEN), U3.57 (GND), U4.7 (PGND), U4.8 (SGND), U5.1 (GND), U6.8 (VSS), U6.14 (VSS), U6.17 (VSS), U6.20 (VSS), U6.21 (EP), U7.8 (GND), U8.3 (GND), U9.2 (GND), U25.2 (GND), U25.3 (GND), Y1.2, Y1.4, Y2.2, Y2.4
unnamed: AE1.1 (A), C27.2, C28.2
unnamed: BZ1.2 (+), Q2.3 (D)
unnamed: BZ1.1 (-), R23.2
unnamed: C27.1, L4.2
unnamed: D2.2 (A), L1.2, U4.5 (SW), U4.6 (SW), U4.9 (SW)
unnamed: D516.2 (A), U2.6 (DONE)
unnamed: D516.1 (K), D517.1 (K), R21.1
unnamed: D517.2 (A), U2.7 (CHRG)
unnamed: D518.1 (K), R22.1
unnamed: J1.A5 (CC1), R4.1
unnamed: J1.B5 (CC2), R5.1
unnamed: C30.2, C31.1, M1.1 (+), U9.1 (OUTB)
unnamed: C31.2, C32.1, M1.2 (-), U9.6 (OUTA)
unnamed: P1.4 (SWCLK/TCK), U3.24 (SWCLK)
unnamed: P1.2 (SWDIO/TMS), U3.25 (SWD)
unnamed: Q1.2 (E), R14.1, R16.1
unnamed: R1.1, SW1.2
unnamed: U1.6 (CLK), U3.52 (QSPI_SCLK)
unnamed: U1.5 (DI(IO0)), U3.53 (QSPI_SD0)
unnamed: U1.2 (DO(IO1)), U3.55 (QSPI_SD1)
unnamed: U1.3 (IO2), U3.54 (QSPI_SD2)
unnamed: U1.7 (IO3), U3.51 (QSPI_SD3)
unnamed: R1.2, R2.1, U1.1 (~CS), U3.56 (QSPI_SS)
unnamed: R20.1, U2.2 (ISET)
unnamed: C9.1, U3.23 (DVDD), U3.50 (DVDD)
unnamed: TP1.1, U3.35 (GPIO23)
unnamed: TP2.1, U3.36 (GPIO24)
unnamed: TP3.1, U3.37 (GPIO25)
unnamed: R10.2, R11.1, U3.39 (GPIO27_ADC1)
unnamed: C2.1, U3.20 (XIN), Y1.1
unnamed: C4.1, U3.21 (XOUT), Y1.3
unnamed: R8.2, R9.1, U4.1 (EN)
unnamed: R12.2, R13.1, U4.3 (FB)
unnamed: C43.1, U4.4 (SS)
unnamed: L2.2, L3.1, U6.12 (ANT1)
unnamed: L3.2, L4.1, U6.13 (ANT2)
unnamed: C18.1, U6.19 (DVDD)
unnamed: R15.1, U6.16 (IREF)
unnamed: C23.2, C47.1, L2.1, U6.11 (VDD_PA)
unnamed: C41.1, R19.1, U6.10 (XC1), Y2.1
unnamed: C24.1, R19.2, U6.9 (XC2), Y2.3
unnamed: C26.1, R18.2, U7.6 (VCC1)
unnamed: R17.2, U7.1 (VCC2_IRED-A)
unnamed: C34.1, U25.4 (OUT)

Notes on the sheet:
Vout = Vref (1) * (1+(R1/R2(gndSide)) R2= 1K~3K 5.2 = 1*(1+ (R/1K)) R1=4.22K IF R1=4.7K, Vout=5.9
AP5056 is a drop in compatible that will charge li ion batteries
This IRDA xcvr can be used to send AND receive remote control codes!!! See https://datasheet.octopart.com/TFBS4710-TT1-Vishay-datasheet-12514678.pdf
Saturation V 0.4V Saturation output voltage 4.6 need to detect between 35,000 and 18 lux 4K7 looks right

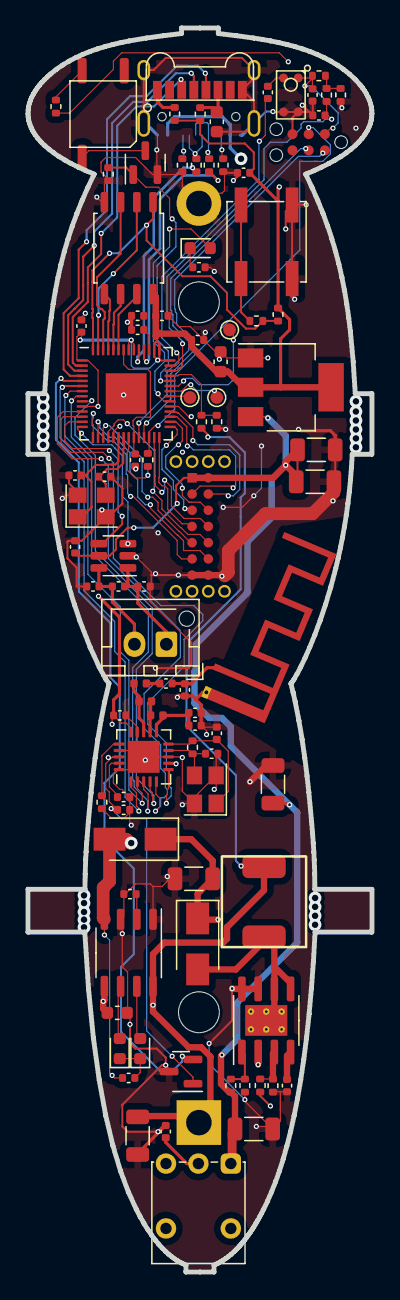
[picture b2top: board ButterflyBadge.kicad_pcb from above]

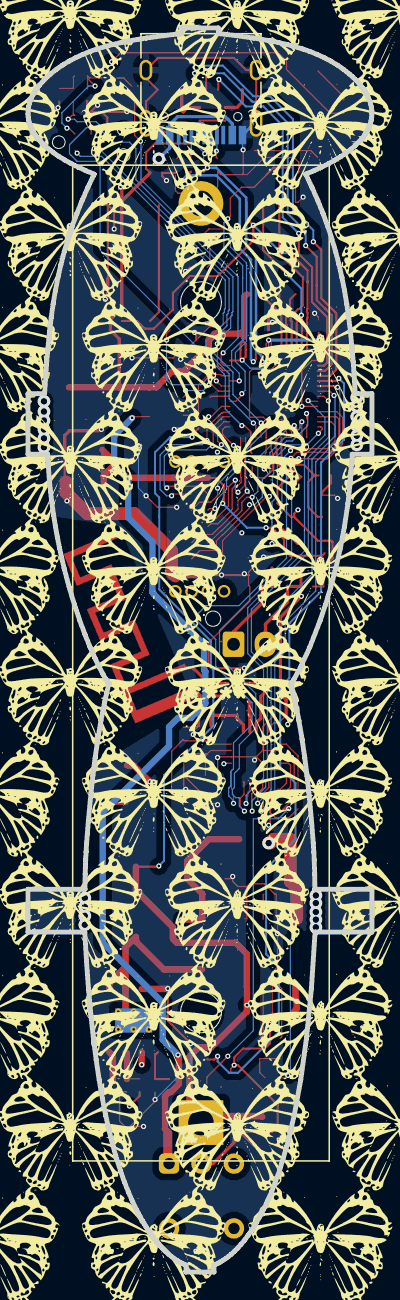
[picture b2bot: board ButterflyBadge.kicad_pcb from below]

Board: 4 copper layers, 26.9 x 97.4 mm, 95 parts (2 on the bottom side), 82 nets.

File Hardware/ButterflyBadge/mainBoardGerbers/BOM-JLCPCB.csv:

Comment,Designator,Footprint,LCSC
"Antenna","AE1","RF_Antenna:Texas_SWRA117D_2.4GHz_Left",""
"Battery_Cell","BT1","Battery:BatteryHolder_MPD_BH-18650-PC2",""
"Buzzer","BZ1","ButterflyBadge:Buzzer-GSC5025YA-12R4000",""
"0.1uF","C1,C6,C10,C13,C20,C33","Capacitor_SMD:C_0402_1005Metric","C307331"
"22uF","C15,C21,C22,C25,C35,C44","Capacitor_SMD:C_1206_3216Metric","C12891"
"10nF","C17","Capacitor_SMD:C_0402_1005Metric","C15195"
"33nF","C18","Capacitor_SMD:C_0402_1005Metric","C1585"
"20pF","C2,C4","Capacitor_SMD:C_0402_1005Metric","C1554"
"2.2n","C23,C46","Capacitor_SMD:C_0402_1005Metric","C1531"
"9pF","C24,C41","Capacitor_SMD:C_0402_1005Metric","C32949"
"0.1uF","C26","Capacitor_SMD:C_0603_1608Metric","C307331"
"4.7pf","C27,C28,C47","Capacitor_SMD:C_0402_1005Metric","C1569"
"10uF","C42,C45","Capacitor_SMD:C_0603_1608Metric","C96446"
"1uF","C5,C9,C11,C16,C29,C30,C31,C32,C34,C43","Capacitor_SMD:C_0402_1005Metric","C52923"
"D_Schottky","D1,D2","Diode_SMD:D_SMA","C8678"
"LED","D516,D517,D518","LED_SMD:LED_0603_1608Metric","C2286"
"USB_C_Receptacle_USB2.0","J1","Connector_USB:USB_C_Receptacle_HRO_TYPE-C-31-M-12",""
"Conn_02x07_Odd_Even","J4","ButterflyBadge:FlatFlexWingConnector-PCBSide",""
"22uH","L1","ButterflyBadge:YSPI0630A","C497873"
"2.7nH","L2","Inductor_SMD:L_0402_1005Metric","C14033"
"8.2nH","L3","Inductor_SMD:L_0402_1005Metric","C27147"
"3.9nH","L4","Inductor_SMD:L_0402_1005Metric","C14033"
"Motor_DC","M1","Connector_JST:JST_XH_B2B-XH-AM_1x02_P2.50mm_Vertical",""
"TC2030-CTX","P1","Tag-Connect:TC2030-MCP-NL",""
"ALS-PT19","Q1","Resistor_SMD:R_0402_1005Metric","C146233"
"Q_NMOS_GSD","Q2","Package_TO_SOT_SMD:SOT-23","C8545"
"1K","R1,R8,R10,R11,R13,R16","Resistor_SMD:R_0402_1005Metric","C11702"
"4.22K","R12","Resistor_SMD:R_0402_1005Metric","C25900"
"4.7K","R14","Resistor_SMD:R_0402_1005Metric","C25900"
"22K","R15","Resistor_SMD:R_0402_1005Metric","C25768"
"0","R17,R18,R23","Resistor_SMD:R_0402_1005Metric","C17168"
"1M","R19","Resistor_SMD:R_0402_1005Metric","C26083"
"10K","R2,R3,R9,R24","Resistor_SMD:R_0402_1005Metric","C25744"
"2.2K","R20","Capacitor_SMD:C_0402_1005Metric","C25879"
"330","R21,R22","Capacitor_SMD:C_0402_1005Metric","C25104"
"5.1k","R4,R5","Resistor_SMD:R_0402_1005Metric","C25905"
"27","R6,R7","Resistor_SMD:R_0402_1005Metric","C25105"
"SW_Push","SW1","Button_Switch_SMD:SW_SPST_EVPBF","C318884"
"SW_SPDT","SW3","Button_Switch_THT:SW_Push_1P2T_Vertical_E-Switch_800UDP8P1A1M6",""
" ","TP1,TP2,TP3","TestPoint:TestPoint_Pad_D1.0mm",""
"W25Q128JVS","U1","Package_SO:SOIC-8_5.23x5.23mm_P1.27mm","C97521"
"CN3058","U2","Package_SO:SOP-8_3.9x4.9mm_P1.27mm","CN3058E"
"AP3722AT","U25","AP3722AT:AP3722AT","C918198"
"RP2040","U3","Package_DFN_QFN:QFN-56-1EP_7x7mm_P0.4mm_EP3.2x3.2mm","C2040"
"AX5201","U4","Package_SO:SOIC-8-1EP_3.9x4.9mm_P1.27mm_EP2.41x3.3mm_ThermalVias","C211668"
"AMS1117-3.3","U5","Package_TO_SOT_SMD:SOT-223-3_TabPin2","C6186"
"Si24R1","U6","Package_DFN_QFN:QFN-20-1EP_4x4mm_P0.5mm_EP2.5x2.5mm","C14436"
"TFDU4301","U7","TFDU4301:TFDU4301","C222418"
"SM351LT","U8","Package_TO_SOT_SMD:SOT-23","C285995"
"TMI8118","U9","Package_TO_SOT_SMD:SOT-23-6","C840556"
"12MHz","Y1","Crystal:Crystal_SMD_3225-4Pin_3.2x2.5mm","C9002"
"16MHz","Y2","Crystal:Crystal_SMD_3225-4Pin_3.2x2.5mm","C13738"

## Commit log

2022-09-13 added rust code
2022-09-13 fixed_dirs
2022-09-13 Initial hardware commit
2022-09-16 fixed frame repainting and added ide files to gitignore
2022-09-16 Finished the power section
2022-09-17 More hardware work
2022-09-21 More schetaic work
2022-09-22 Main schematic is done?
2022-09-24 refactor led generation code to use iterators
2022-09-25 I rewrote a lot :+1:
2022-09-25 moved layout to new file
2022-09-25 wow butterflies ya know?
2022-09-25 added led counter
2022-09-30 Schematic is done! Now to work on the main PCB
2022-09-30 added gitnore for mac weirdness and ideas text document
2022-10-02 added a third vis, package structure changed
2022-10-02 added save to svg button
2022-10-03 Added CSV export
2022-10-04 added checks to prevent crashes
2022-10-04 Pulled in wing half
2022-10-04 aayayaya
2022-10-04 More schematic and PCB work Bang
2022-10-08 restart progress/
2022-10-08 zero warnings ^_^
2022-10-08 more refactor
2022-10-08 reformat with rustfmt
2022-10-08 butterfly renders nicer
2022-10-09 refactoring
2022-10-10 Hardware mods
2022-10-11 Almost had the PCB done, need to restart. Sad face
2022-10-13 Component placement is done, now for layout
2022-10-13 Commit before I try to ripup everything on a whim
2022-10-14 More routing
2022-10-14 Routing done, next is error checking and assembly
2022-10-14 Commit before changing board outline
2022-10-18 Placed all the stbd wing leds
2022-10-19 Routing done
2022-10-19 good enough
2022-10-20 Started the port wing, was able to pull locations from starboard
2022-10-20 Re-moved everything
2022-10-22 Released boards to manufacture
2022-10-22 Added BOMs
2022-10-25 Added new port wing .zip
2022-11-01 Pull
2022-11-01 Added pio
2022-11-01 Added second wing
2022-11-01 asdf
2022-11-04 Added PDF
2022-11-06 kegan :3
2022-11-07 Added LED positions
2022-11-07 Added gif generator
2022-11-07 Updated sizing on frames
2022-11-28 Started working on a hinge
2022-11-29 Added gif code, worked on the 3d printed hinges'
2022-11-30 Added elf file output
2022-11-30 Added firmware
2022-11-30 Modified firmware
2022-11-30 Changed to rickroll gif
2022-11-30 Switched to rainbow
2022-11-30 Updated gif
2022-11-30 new gif
2022-11-30 Maybe new rainbow?
2022-11-30 Added spongebob gif
2022-11-30 added spiral gif
2022-11-30 Reduced brightness
2022-12-01 did stuff ~
2022-12-01 this might have broke it, sorry >_<
2022-12-04 Added hinges, changed runner
2023-03-18 fix red bug
2023-03-21 undo bad
